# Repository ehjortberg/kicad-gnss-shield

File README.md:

# GNSS Shield
 - Should fit a Raspberry Pi 40 pin header or compatible.
 - Has footprints for Adafruits zedf9p, Navspark Mini, Navspark NS-HP, and Mikroe gnss-rtk-click
 - Has FTDI and HC-12 connectors for both UART1 and UART2 on the GNSS Modules
 - Connectes UART2 to Raspberry Pi 4 UART2

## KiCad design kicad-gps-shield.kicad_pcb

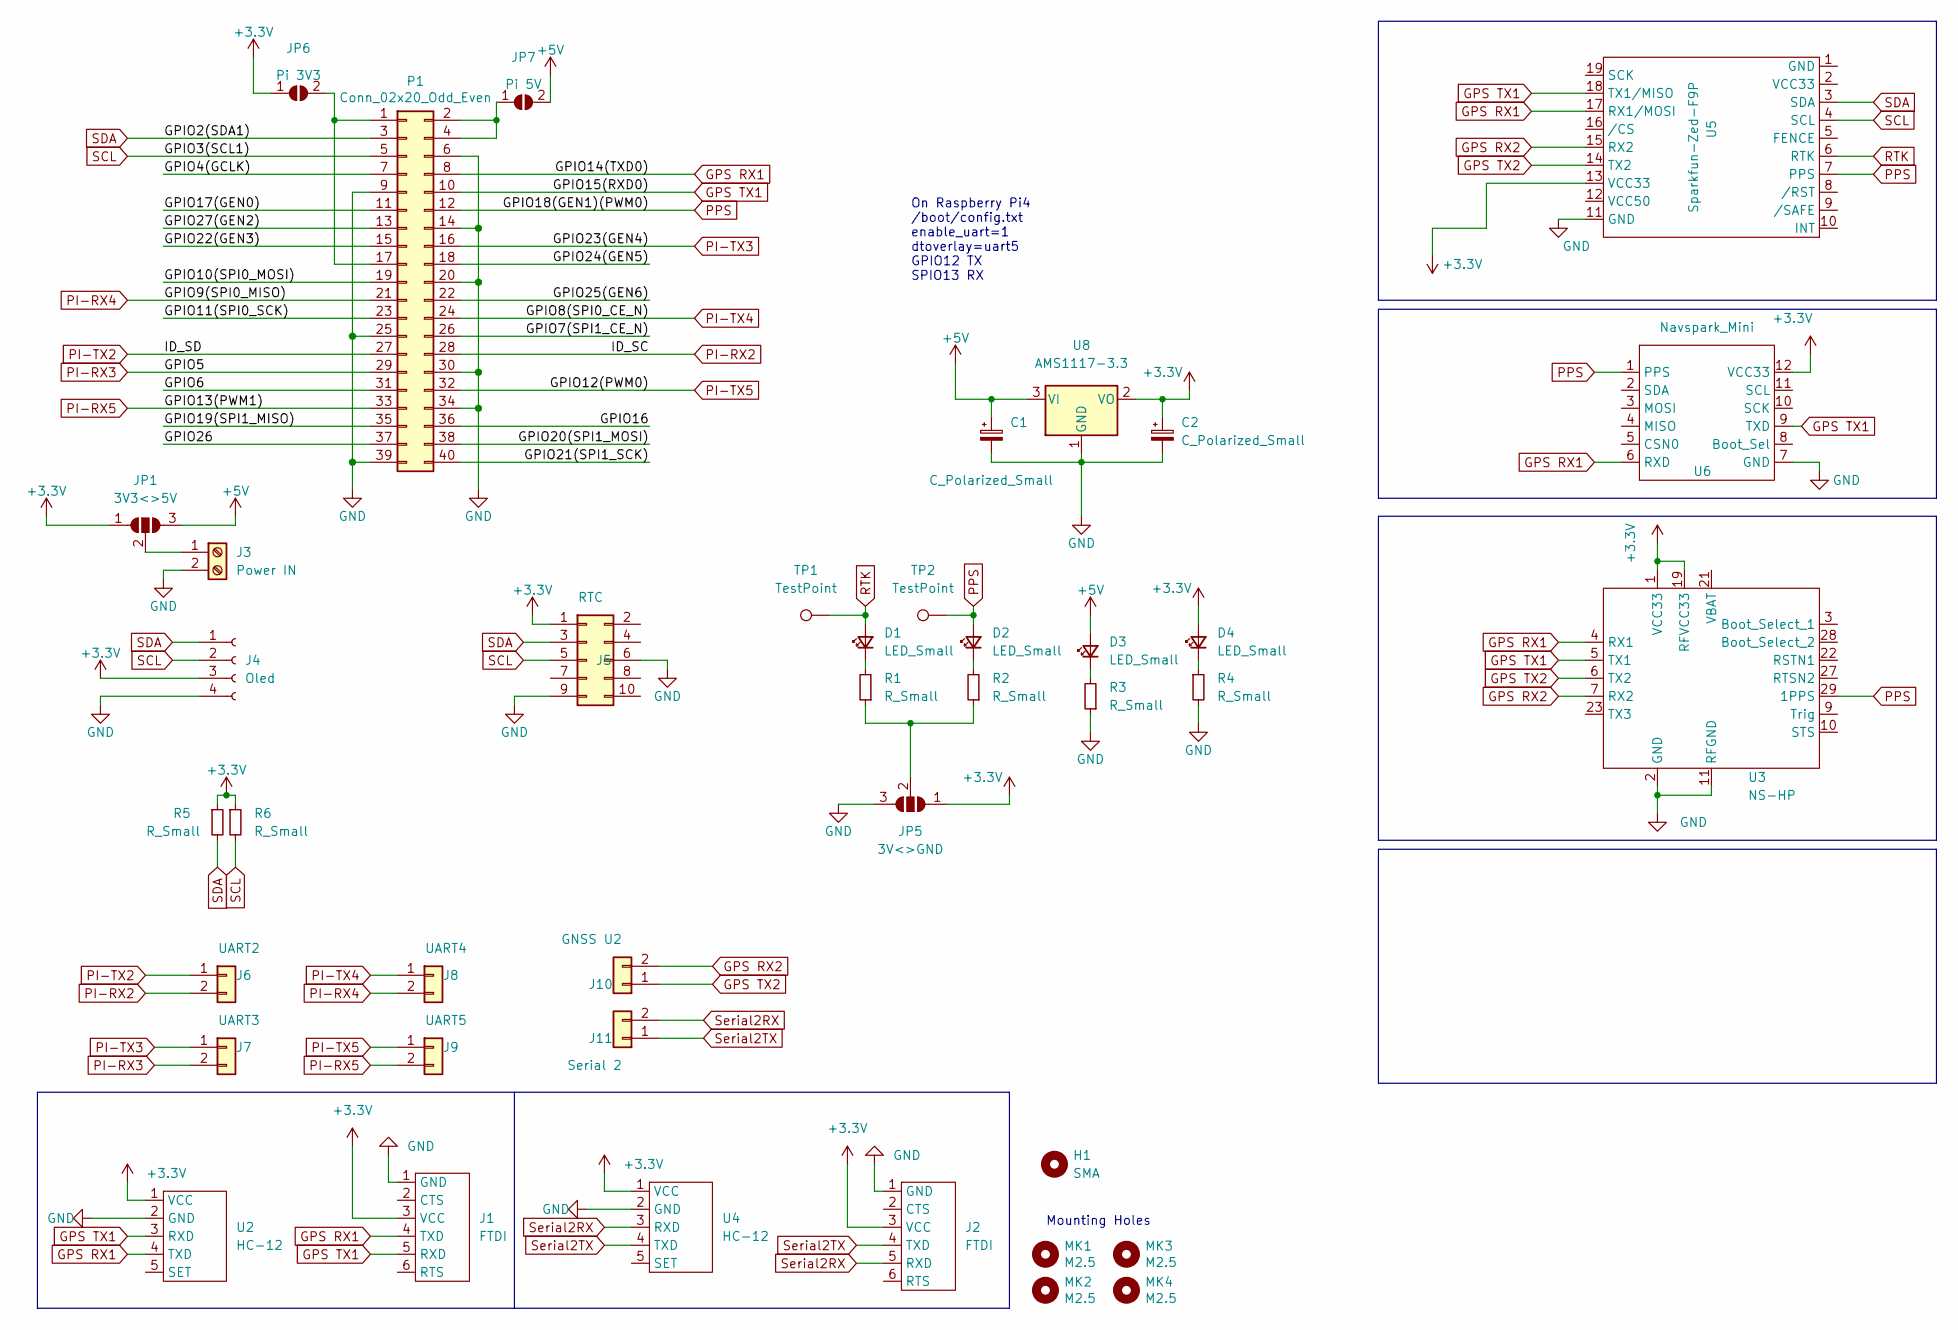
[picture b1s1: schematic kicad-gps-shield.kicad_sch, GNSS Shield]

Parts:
C1, C2: C_Polarized_Small; CP_EIA-6032-28_Kemet-C_Pad2.25x2.35mm_HandSolder
D1, D2, D3, D4: LED_Small; LED_0805_2012Metric_Pad1.15x1.40mm_HandSolder
H1: SMA; MountingHole_6.4mm_M6_ISO14580
J1, J2: FTDI
J3: Power IN; PinSocket_1x02_P2.54mm_Vertical
J4: Oled; PinSocket_1x04_P2.54mm_Vertical
J5: RTC; PinSocket_2x05_P2.54mm_Vertical
J6: UART2; PinSocket_1x02_P2.54mm_Vertical
J7: UART3; PinSocket_1x02_P2.54mm_Vertical
J8: UART4; PinSocket_1x02_P2.54mm_Vertical
J9: UART5; PinSocket_1x02_P2.54mm_Vertical
J10: GNSS U2; PinSocket_1x02_P2.54mm_Vertical
J11: Serial 2; PinSocket_1x02_P2.54mm_Vertical
JP1: 3V3<>5V; SolderJumper-3_P2.0mm_Open_TrianglePad1.0x1.5mm
JP5: 3V<>GND; SolderJumper-3_P2.0mm_Open_TrianglePad1.0x1.5mm
JP6: Pi 3V3; SolderJumper-2_P1.3mm_Open_TrianglePad1.0x1.5mm
JP7: Pi 5V; SolderJumper-2_P1.3mm_Open_TrianglePad1.0x1.5mm
MK1, MK2, MK3, MK4: M2.5; MountingHole_2.7mm_M2.5
P1: Conn_02x20_Odd_Even; PinSocket_2x20_P2.54mm_Vertical
R1, R2, R3, R4, R5, R6: R_Small; R_0805_2012Metric_Pad1.20x1.40mm_HandSolder
TP1, TP2: TestPoint; TestPoint_THTPad_2.5x2.5mm_Drill1.2mm
U2, U4: HC-12
U3: NS-HP
U5: Sparkfun-Zed-F9P; Sparkfun zed-f9p
U6: Navspark_Mini; Navspark Mini
U8: AMS1117-3.3; SOT-223-3_TabPin2

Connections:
+3V3: C2.1, D4.2 (A), J1.3 (VCC), J2.3 (VCC), J4.3, J5.1, JP1.1 (A), JP5.1 (A), JP6.1 (A), R5.1, R6.1, U2.1 (VCC), U3.1 (VCC33), U3.19 (RFVCC33), U3.20 (RFVCC33), U3.25 (VCC33), U4.1 (VCC), U5.13 (VCC33), U6.12 (VCC33), U8.2 (VO)
+5V: C1.1, D3.2 (A), JP1.3 (B), JP7.2 (B), U8.3 (VI)
/GPIO4(GCLK): P1.7
/GPIO6: P1.31
/GPIO7(SPI1_CE_N): P1.26
/GPIO10(SPI0_MOSI): P1.19
/GPIO11(SPI0_SCK): P1.23
/GPIO16: P1.36
/GPIO17(GEN0): P1.11
/GPIO19(SPI1_MISO): P1.35
/GPIO20(SPI1_MOSI): P1.38
/GPIO21(SPI1_SCK): P1.40
/GPIO22(GEN3): P1.15
/GPIO24(GEN5): P1.18
/GPIO25(GEN6): P1.22
/GPIO26: P1.37
/GPIO27(GEN2): P1.13
GND: C1.2, C2.2, J1.1 (GND), J2.1 (GND), J3.2, J4.4, J5.6, J5.9, JP5.3 (B), P1.6, P1.9, P1.14, P1.20, P1.25, P1.30, P1.34, P1.39, R3.1, R4.2, U2.2 (GND), U3.2 (GND), U3.11 (RFGND), U3.12 (RFGND), U3.16 (RFGND), U3.17 (RFGND), U3.18 (RFGND), U3.30 (GND), U4.2 (GND), U5.11 (GND), U6.7 (GND), U8.1 (GND)
GPS RX1: J1.4 (TXD), P1.8, U2.4 (TXD), U3.4 (RX1), U5.17 (RX1/MOSI), U6.6 (RXD)
GPS RX2: J10.2, U3.7 (RX2), U5.15 (RX2)
GPS TX1: J1.5 (RXD), P1.10, U2.3 (RXD), U3.5 (TX1), U5.18 (TX1/MISO), U6.9 (TXD)
GPS TX2: J10.1, U3.6 (TX2), U5.14 (TX2)
unnamed: D1.1 (K), R1.2
unnamed: D2.1 (K), R2.2
unnamed: D3.1 (K), R3.2
unnamed: D4.1 (K), R4.1
unnamed: J3.1, JP1.2 (C)
unnamed: JP5.2 (C), R1.1, R2.1
unnamed: JP6.2 (B), P1.1, P1.17
unnamed: JP7.1 (A), P1.2, P1.4
PI-RX2: J6.2, P1.28
PI-RX3: J7.2, P1.29
PI-RX4: J8.2, P1.21
PI-RX5: J9.2, P1.33
PI-TX2: J6.1, P1.27
PI-TX3: J7.1, P1.16
PI-TX4: J8.1, P1.24
PI-TX5: J9.1, P1.32
PPS: D2.2 (A), P1.12, TP2.1, U3.29 (1PPS), U5.7 (PPS), U6.1 (PPS)
RTK: D1.2 (A), TP1.1, U5.6 (RTK)
SCL: J4.2, J5.5, P1.5, R6.2, U5.4 (SCL)
SDA: J4.1, J5.3, P1.3, R5.2, U5.3 (SDA)
Serial2RX: J2.5 (RXD), J11.2, U4.3 (RXD)
Serial2TX: J2.4 (TXD), J11.1, U4.4 (TXD)

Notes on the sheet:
Mounting Holes
On Raspberry Pi4 /boot/config.txt enable_uart=1 dtoverlay=uart5 GPIO12 TX SPIO13 RX

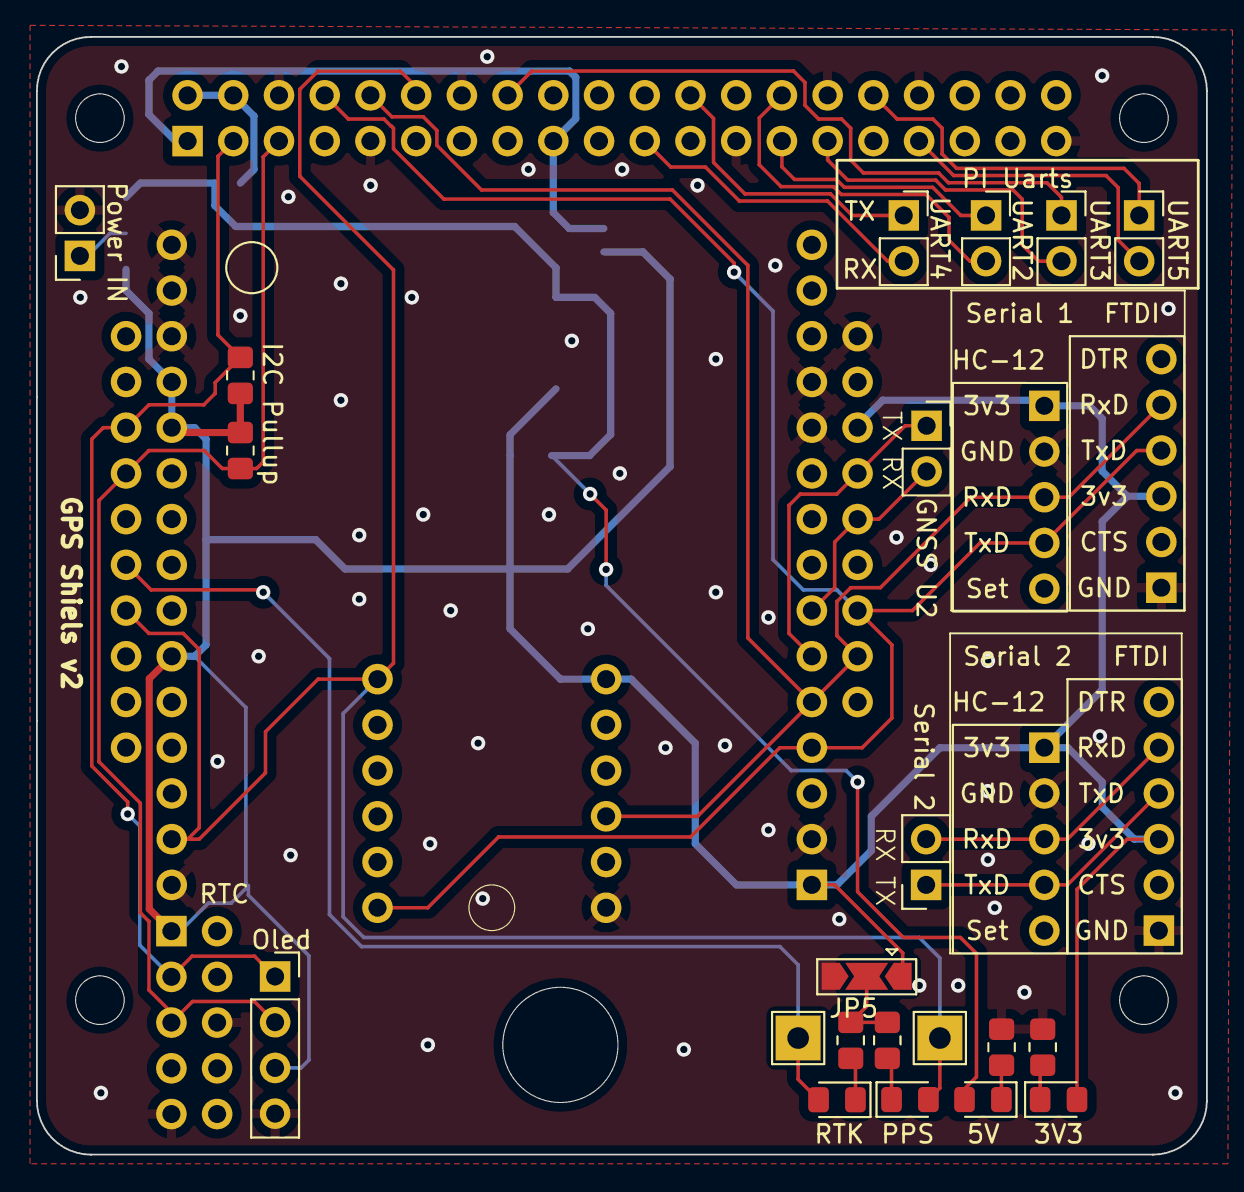
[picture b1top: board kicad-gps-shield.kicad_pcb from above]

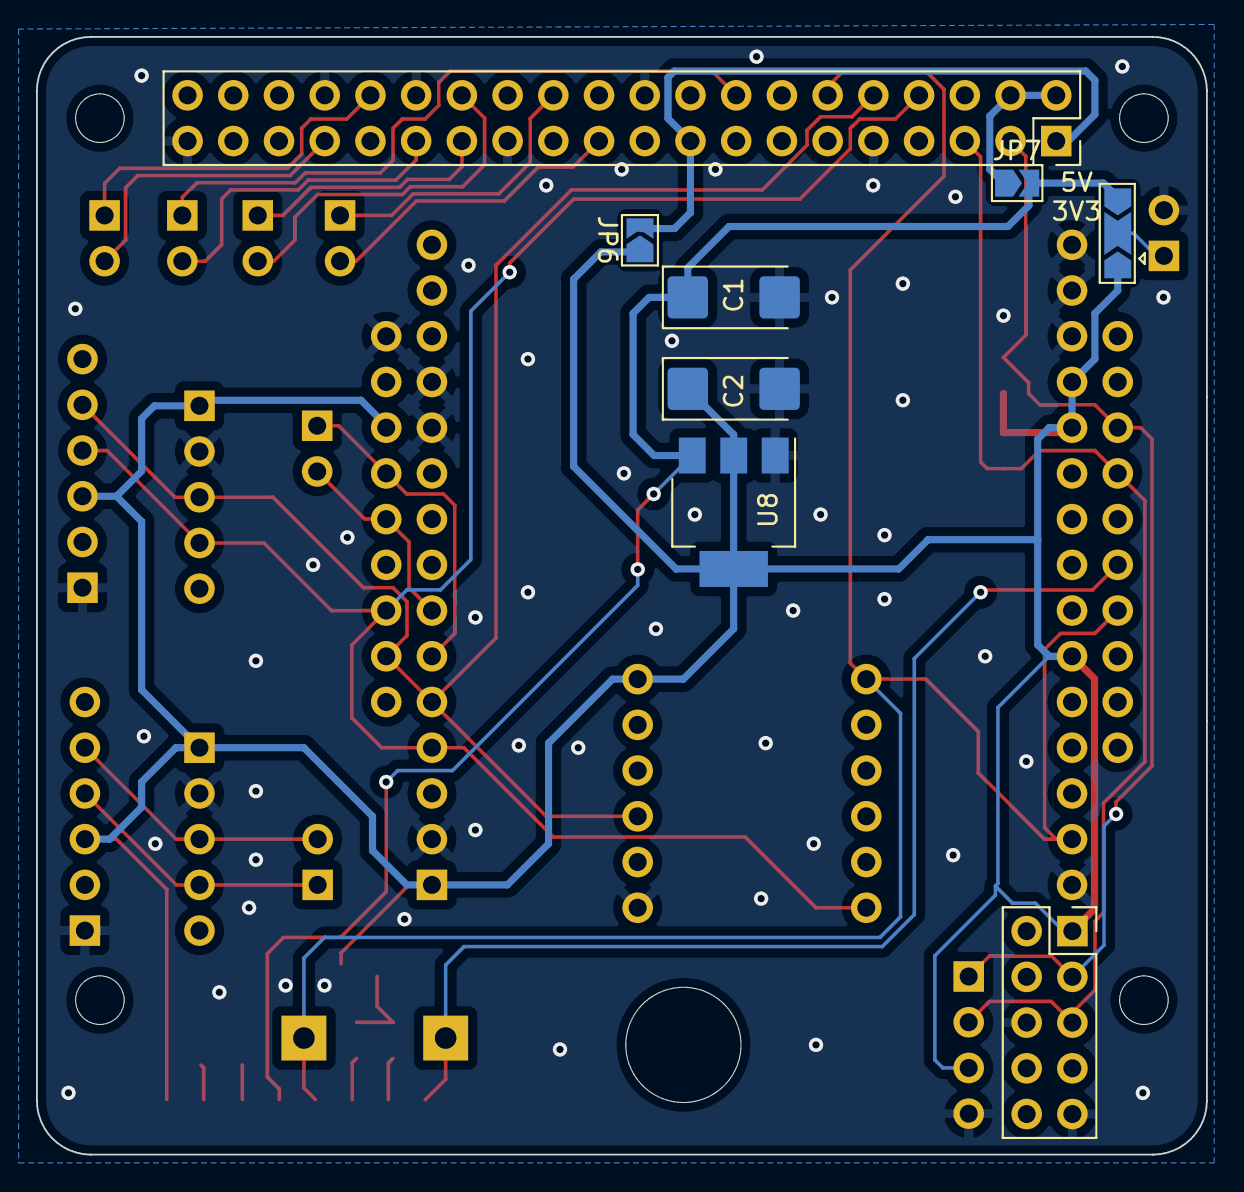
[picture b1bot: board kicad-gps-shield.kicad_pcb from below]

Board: 2 copper layers, 65.0 x 62.1 mm, 41 parts (8 on the bottom side), 29 nets.
